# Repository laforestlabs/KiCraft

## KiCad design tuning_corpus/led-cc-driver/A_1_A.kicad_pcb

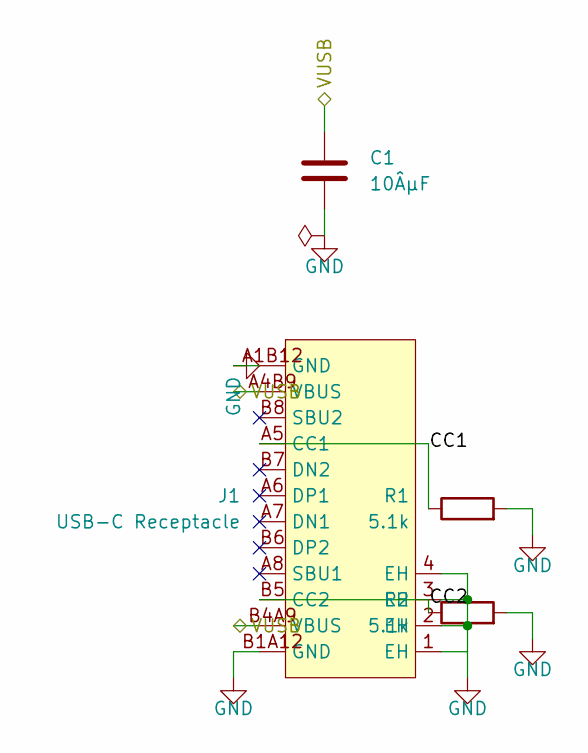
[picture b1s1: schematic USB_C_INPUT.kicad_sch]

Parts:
C1: 10ÂµF; C_0805_2012Metric
J1: USB-C Receptacle; USB-C_SMD-TYPE-C-31-M-12_1
R1, R2: 5.1k; R_0805_2012Metric

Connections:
CC1: J1.A5 (CC1), R1.1
CC2: J1.B5 (CC2), R2.1
GND: C1.2, J1.1 (EH), J1.2 (EH), J1.3 (EH), J1.4 (EH), J1.A1B12 (GND), J1.B1A12 (GND), R1.2, R2.2; also elsewhere on the board
VUSB: C1.1, J1.A4B9 (VBUS), J1.B4A9 (VBUS); also elsewhere on the board

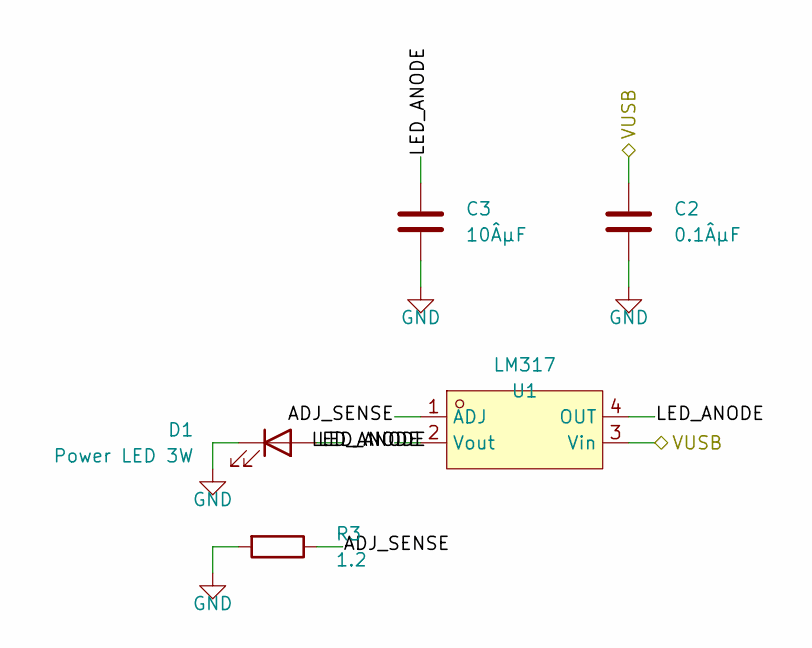
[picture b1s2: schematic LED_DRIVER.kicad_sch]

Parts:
C2: 0.1ÂµF; C_0805_2012Metric
C3: 10ÂµF; C_0805_2012Metric
D1: Power LED 3W; LED_Cree-PLCC4_5x5mm_CW
R3: 1.2; R_2512_6332Metric
U1: LM317; SOT-223-4_L6.5-W3.5-P2.30-LS7.0-BR

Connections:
ADJ_SENSE: R3.1, U1.1 (ADJ)
GND: C2.2, C3.2, D1.1 (K), R3.2; also elsewhere on the board
LED_ANODE: C3.1, D1.2 (A), U1.2 (Vout), U1.4 (OUT)
VUSB: C2.1, U1.3 (Vin); also elsewhere on the board

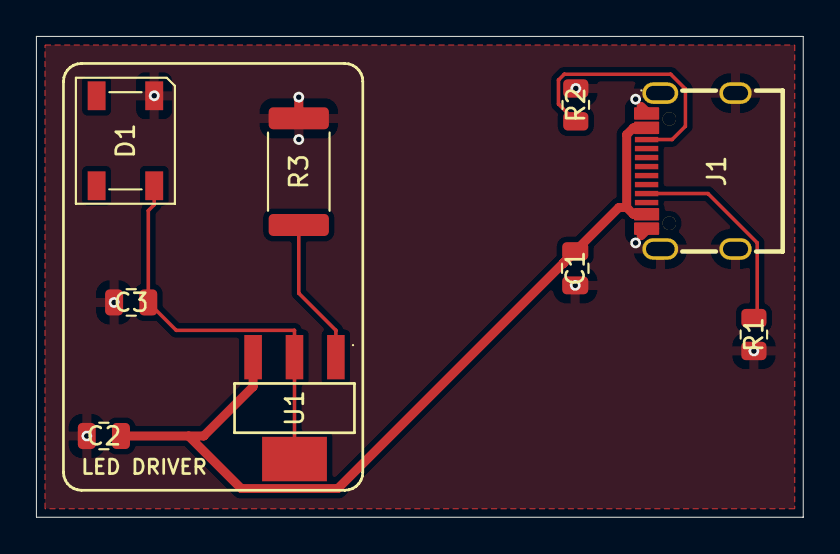
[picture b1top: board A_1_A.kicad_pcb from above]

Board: 2 copper layers, 42.6 x 26.7 mm, 9 parts (0 on the bottom side), 6 nets.

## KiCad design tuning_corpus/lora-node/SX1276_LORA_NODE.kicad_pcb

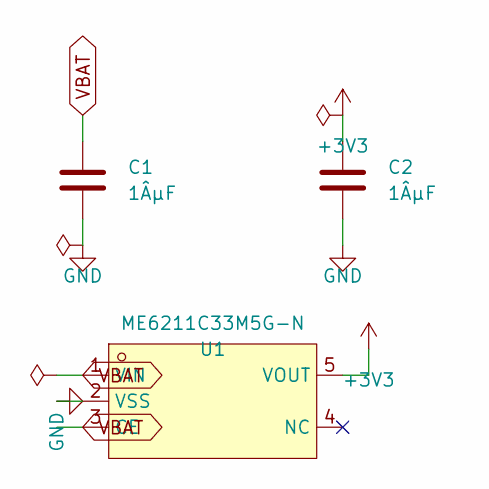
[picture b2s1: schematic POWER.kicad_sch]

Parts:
C1, C2: 1ÂµF; C_0805_2012Metric
U1: ME6211C33M5G-N; SOT-23-5_L3.0-W1.7-P0.95-LS2.8-BL

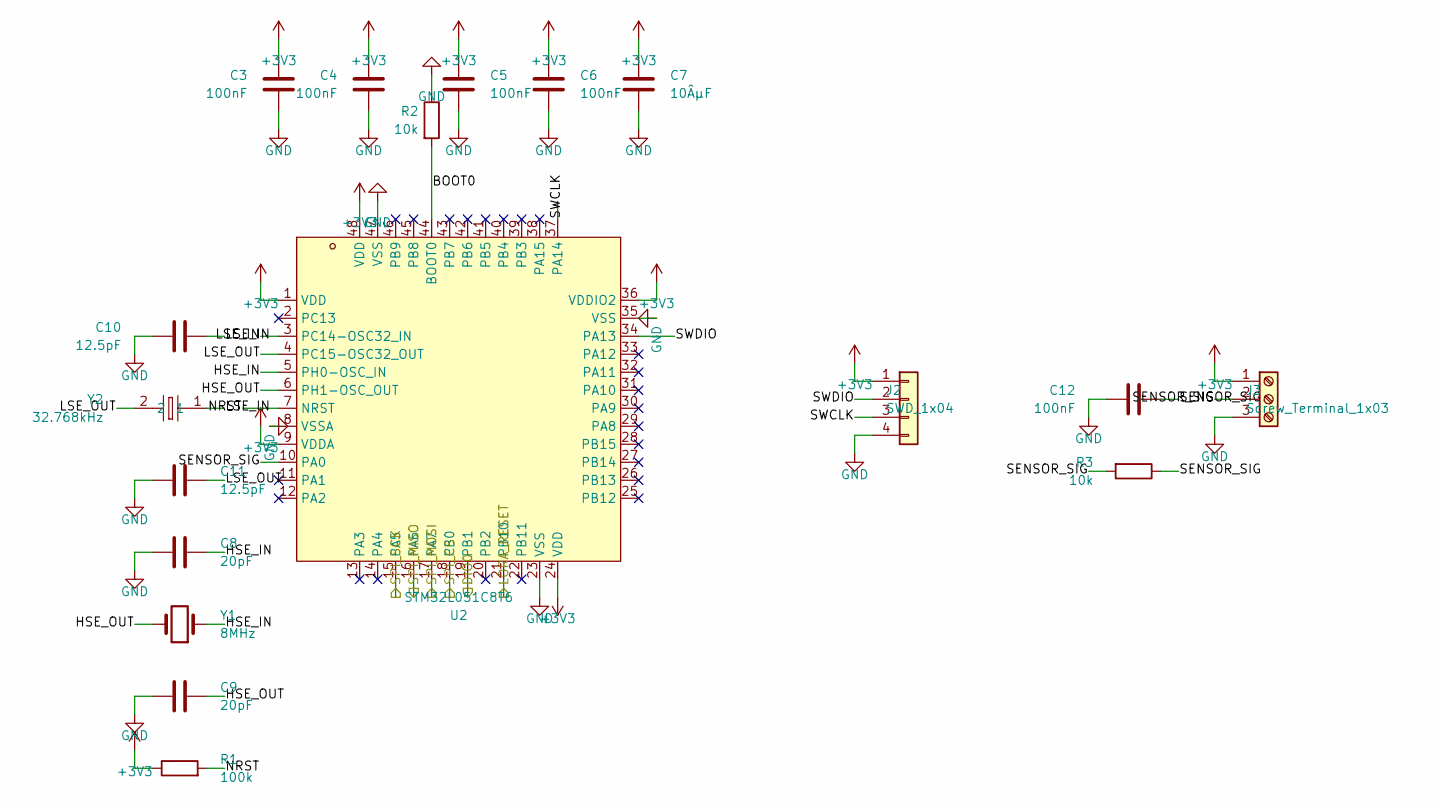
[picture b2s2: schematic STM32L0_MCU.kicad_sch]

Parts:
C3, C4, C5, C6, C12: 100nF; C_0805_2012Metric
C7: 10ÂµF; C_0805_2012Metric
C8, C9: 20pF; C_0805_2012Metric
C10, C11: 12.5pF; C_0805_2012Metric
J2: SWD_1x04; PinHeader_1x04_P2.54mm_Vertical
J3: Screw_Terminal_1x03; TerminalBlock_MaiXu_MX126-5.0-03P_1x03_P5.00mm
R1: 100k; R_0805_2012Metric
R2, R3: 10k; R_0805_2012Metric
U2: STM32L051C8T6; LQFP-48_L7.0-W7.0-P0.50-LS9.0-BL
Y1: 8MHz; Crystal_SMD_3225-4Pin_3.2x2.5mm
Y2: 32.768kHz; OSC-SMD_L3.2-W1.5

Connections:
BOOT0: R2.2, U2.44 (BOOT0)
DIO0: U2.19 (PB1); also elsewhere on the board
HSE_IN: C8.1, U2.5 (PH0-OSC_IN), Y1.1
HSE_OUT: C9.1, U2.6 (PH1-OSC_OUT), Y1.2
LORA_RESET: U2.21 (PB10); also elsewhere on the board
LSE_IN: C10.1, U2.3 (PC14-OSC32_IN), Y2.1
LSE_OUT: C11.1, U2.4 (PC15-OSC32_OUT), Y2.2
NRST: R1.2, U2.7 (NRST)
SENSOR_SIG: C12.1, J3.2, R3.1, R3.2, U2.10 (PA0)
SPI_CS: U2.18 (PB0); also elsewhere on the board
SPI_MISO: U2.16 (PA6); also elsewhere on the board
SPI_MOSI: U2.17 (PA7); also elsewhere on the board
SPI_SCK: U2.15 (PA5); also elsewhere on the board
SWCLK: J2.3, U2.37 (PA14)
SWDIO: J2.2, U2.34 (PA13)

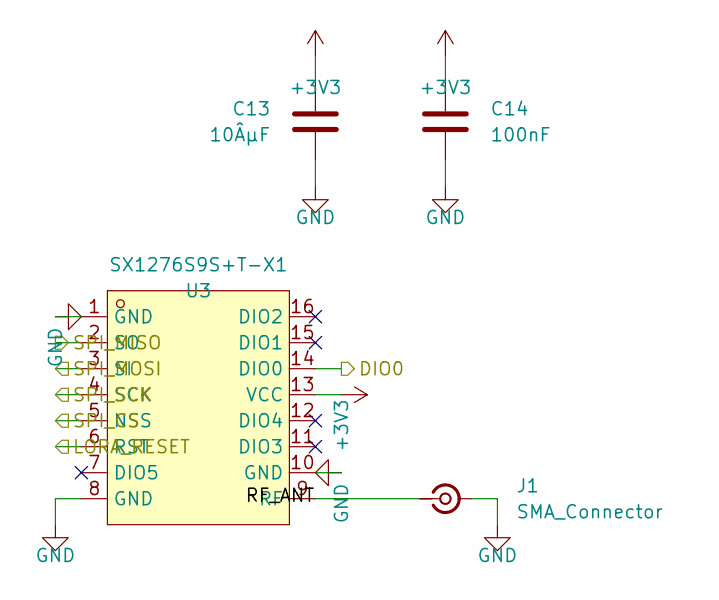
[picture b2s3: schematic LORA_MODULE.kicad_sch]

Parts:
C13: 10ÂµF; C_0805_2012Metric
C14: 100nF; C_0805_2012Metric
J1: SMA_Connector; SMA_Amphenol_132203-12_Horizontal
U3: SX1276S9S+T-X1; WIRELM-SMD_SX1278S165SY-T-X1

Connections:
DIO0: U3.14 (DIO0); also elsewhere on the board
LORA_RESET: U3.6 (RST); also elsewhere on the board
RF_ANT: J1.1 (In), U3.9 (RF)
SPI_CS: U3.5 (NSS); also elsewhere on the board
SPI_MISO: U3.2 (SO); also elsewhere on the board
SPI_MOSI: U3.3 (SI); also elsewhere on the board
SPI_SCK: U3.4 (SCK); also elsewhere on the board

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
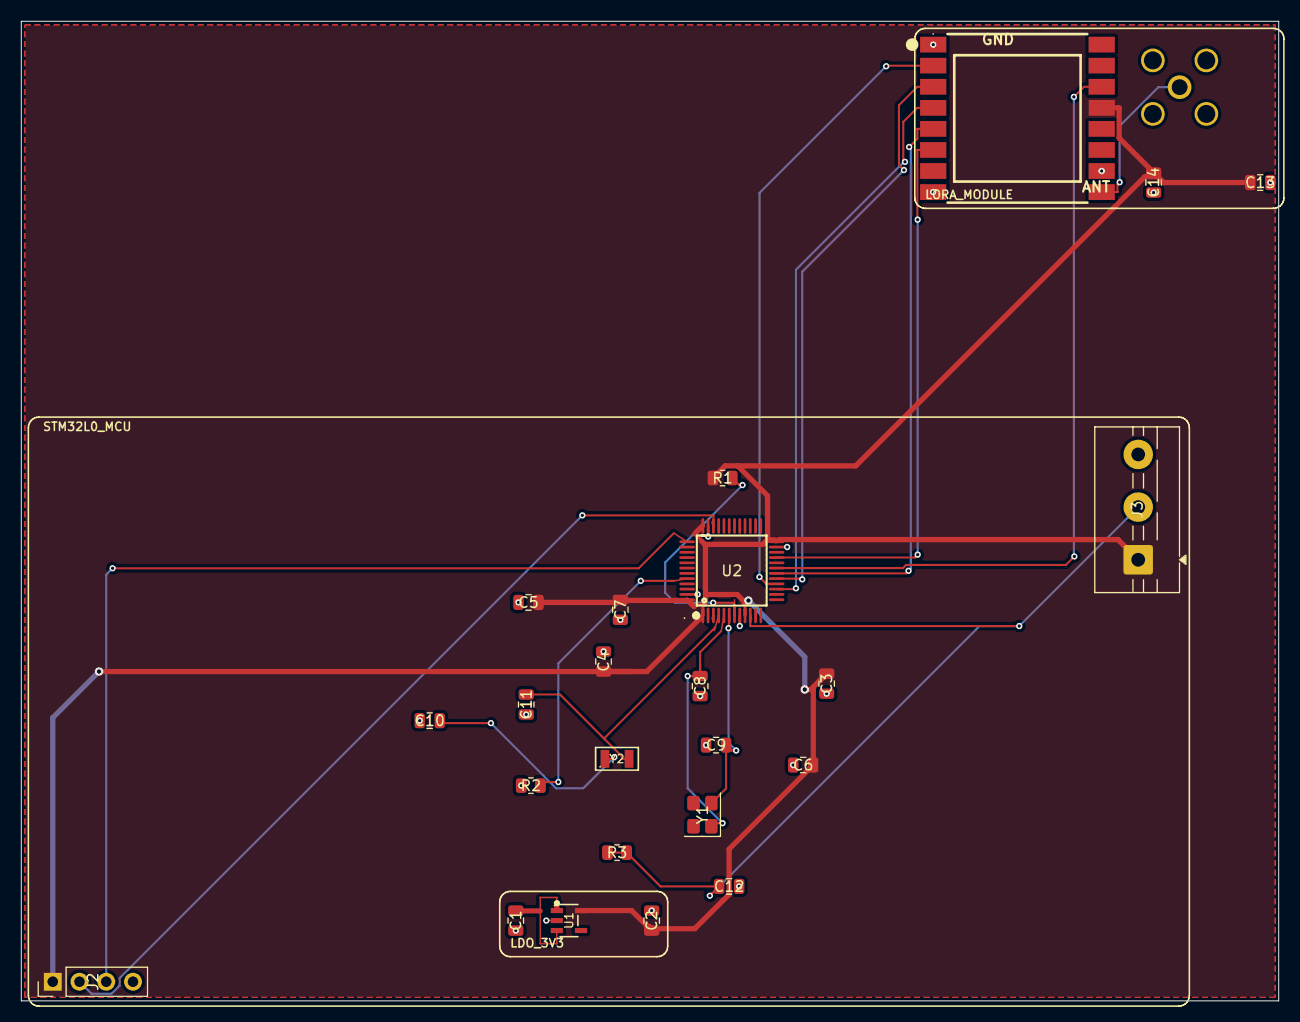
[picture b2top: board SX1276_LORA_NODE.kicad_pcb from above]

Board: 2 copper layers, 119.4 x 93.0 mm, 25 parts (1 on the bottom side), 19 nets.

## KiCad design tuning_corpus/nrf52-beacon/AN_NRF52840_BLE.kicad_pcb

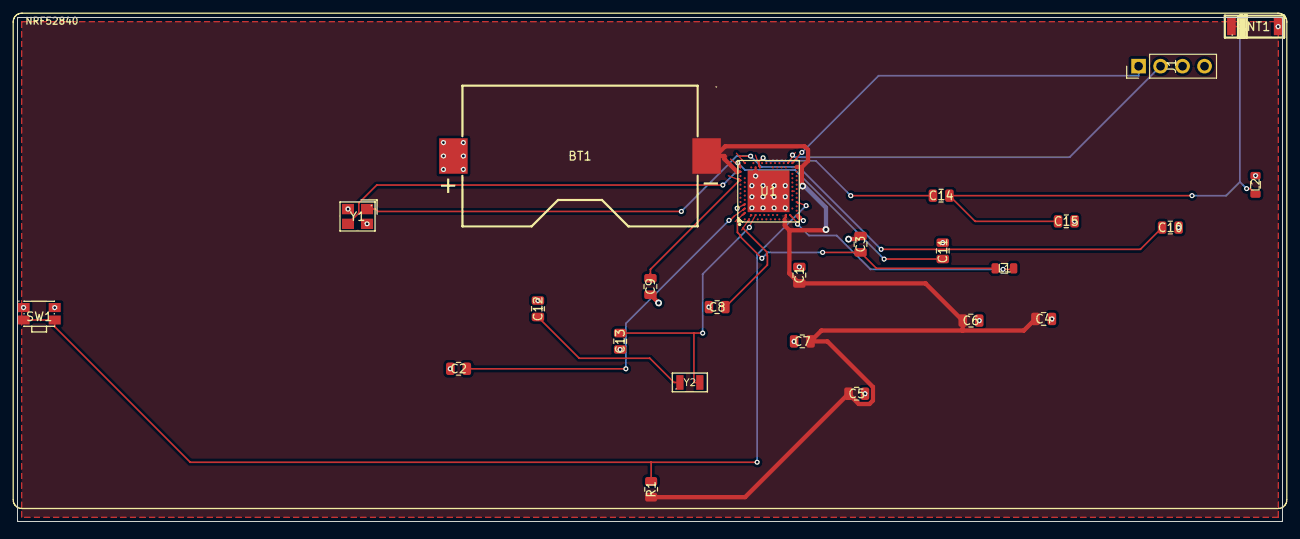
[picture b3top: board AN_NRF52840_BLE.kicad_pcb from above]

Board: 2 copper layers, 146.2 x 58.2 mm, 25 parts (0 on the bottom side), 17 nets.

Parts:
ANT1: RFANT5220110A0T; FILTER-SMD_L5.2-W2.0-L
BT1: CR2032; BAT-SMD_BS06A3B0A006
C1, C3: 10ÂµF; C_0805_2012Metric
C2: 4.7ÂµF; C_0805_2012Metric
C4, C5, C6, C7, C8, C9: 100nF; C_0805_2012Metric
C10, C11: 20pF; C_0805_2012Metric
C12, C13: 10pF; C_0805_2012Metric
C14, C15: 1.5pF; C_0805_2012Metric
J1: SWD 1x04; PinHeader_1x04_P2.54mm_Vertical
L1: 10ÂµH; L_0805_2012Metric
L2: 3.9nH; L_0805_2012Metric
R1: 10kÎ©; R_0805_2012Metric
SW1: EVQP7A01P; SW-SMD_EVQP7A01P
U1: nRF52840-QIAA-R; AQFN-73_L7.0-W7.0-P0.50-BL-EP4.8
Y1: 32MHz; CRYSTAL-SMD_4P-L3.2-W2.5-BL
Y2: 32.768kHz; OSC-SMD_L3.2-W1.5

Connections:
ANT: C14.1, U1.H23
ANT_OUT: ANT1.1, C14.2, C15.1, L2.1
BUTTON: R1.2, SW1.2, SW1.2', U1.AD8
DCC: C3.1, L1.1, U1.B3
DCCH: L1.2, U1.AB2
DEC1: C8.1, U1.C1
DEC2: C9.1, U1.A18
DEC4: C2.1, U1.B5
GND: ANT1.2, BT1.2, C1.2, C2.2, C3.2, C4.2, C5.2, C6.2, C7.2, C8.2, C9.2, C10.2, C11.2, C12.2, C13.2, C15.2, J1.4, L2.2, SW1.1, SW1.1', U1.0, U1.AD2, U1.B7, U1.F23, Y1.2, Y1.4
RESET: J1.3, U1.AC13
SWCLK: J1.2, U1.AA24
SWDIO: J1.1, U1.AC24
VDD: BT1.1, C1.1, C4.1, C5.1, C6.1, C7.1, R1.1, U1.A22, U1.AD14, U1.AD23, U1.B1, U1.W1, U1.Y2
XC1_32M: C10.1, U1.B24, Y1.1
XC2_32M: C11.1, U1.A23, Y1.3
XL1_32K: C12.1, U1.D2, Y2.1
XL2_32K: C13.1, U1.F2, Y2.2

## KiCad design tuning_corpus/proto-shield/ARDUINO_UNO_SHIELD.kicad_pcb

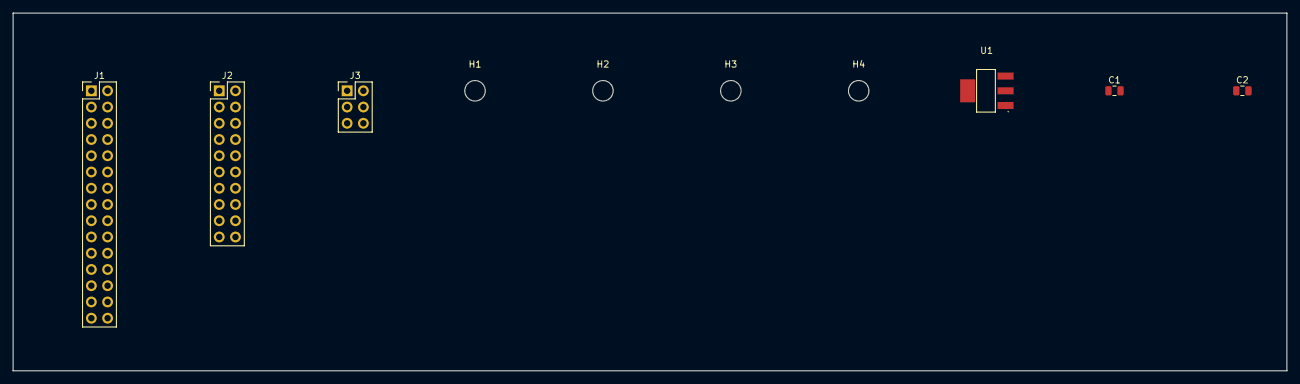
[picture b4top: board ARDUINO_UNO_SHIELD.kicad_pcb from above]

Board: 2 copper layers, 199.2 x 55.9 mm, 10 parts (0 on the bottom side), 17 nets, no tracks yet.

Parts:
C1, C2: 10uF; C_0805_2012Metric
H1, H2, H3, H4: Mounting Hole M3; MountingHole_3.2mm_M3
J1: Stacking Header 2x15; PinHeader_2x15_P2.54mm_Vertical
J2: Stacking Header 2x10; PinHeader_2x10_P2.54mm_Vertical
J3: ICSP Header 2x3; PinHeader_2x03_P2.54mm_Vertical
U1: AMS1117-3.3; SOT-223-3_L6.5-W3.4-P2.30-LS7.0-BR

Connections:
+3V3_ARDUINO: J1.9, J1.28, J2.9
+3V3_REG: C2.1, J2.11, U1.2, U1.4
+5V: C1.1, J1.1, J1.5, J2.1, J2.5, J3.2, U1.3
A0: J1.12, J2.12
A1: J1.14, J2.14
A2: J1.16, J2.16
A3: J1.18, J2.18
A4: J1.20, J2.20
AREF: J1.6, J2.6
D11: J1.23, J3.4
D12: J1.25, J3.1
D13: J1.27, J3.3
GND: C1.2, C2.2, J1.2, J1.7, J1.29, J1.30, J2.2, J2.7, J3.6, U1.1
RESET: J1.3, J2.3, J3.5
SCL: J1.10, J2.10
SDA: J1.8, J2.8
VIN: J1.4, J2.4

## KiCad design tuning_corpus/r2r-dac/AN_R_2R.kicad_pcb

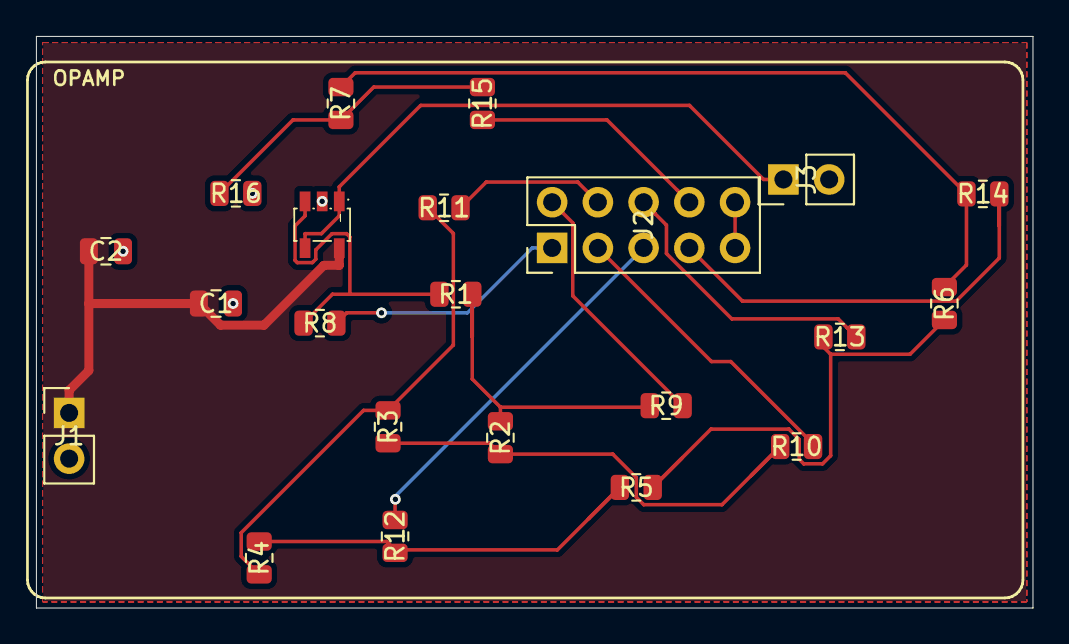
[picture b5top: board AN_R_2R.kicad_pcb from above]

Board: 2 copper layers, 55.4 x 31.8 mm, 22 parts (0 on the bottom side), 19 nets.

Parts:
C1: 0.1uF; C_0805_2012Metric
C2: 10uF; C_0805_2012Metric
J1: Power_2x1; PinHeader_1x02_P2.54mm_Vertical
J2: Input_2x05; PinHeader_2x05_P2.54mm_Vertical
J3: Output_2x1; PinHeader_1x02_P2.54mm_Vertical
R1, R2, R3, R4, R5, R6, R7: 10k; R_0805_2012Metric
R8, R9, R10, R11, R12, R13, R14, R15, R16: 20k; R_0805_2012Metric
U1: MCP6001T-I/OT; SOT-23-5_L3.0-W1.7-P0.95-LS2.8-BR

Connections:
+5V: C1.1, C2.1, J1.1, U1.5
ANA_OUT: J3.1, U1.1, U1.4
D0: J2.8, R15.2
D1: J2.7, R14.2
D2: J2.6, R13.2
D3: J2.5, R12.2
D4: J2.4, R11.2
D5: J2.3, R10.2
D6: J2.2, R9.2
D7: J2.1, R8.2
GND: C1.2, C2.2, J1.2, J2.9, J2.10, J3.2, R16.2, U1.2
N2: R1.2, R2.1, R9.1
N3: R2.2, R3.1, R10.1
N4: R3.2, R4.1, R11.1
N5: R4.2, R5.1, R12.1
N6: R5.2, R6.1, R13.1
N7: R6.2, R7.1, R14.1
N8: R7.2, R15.1, R16.1
VOUT: R1.1, R8.1, U1.3

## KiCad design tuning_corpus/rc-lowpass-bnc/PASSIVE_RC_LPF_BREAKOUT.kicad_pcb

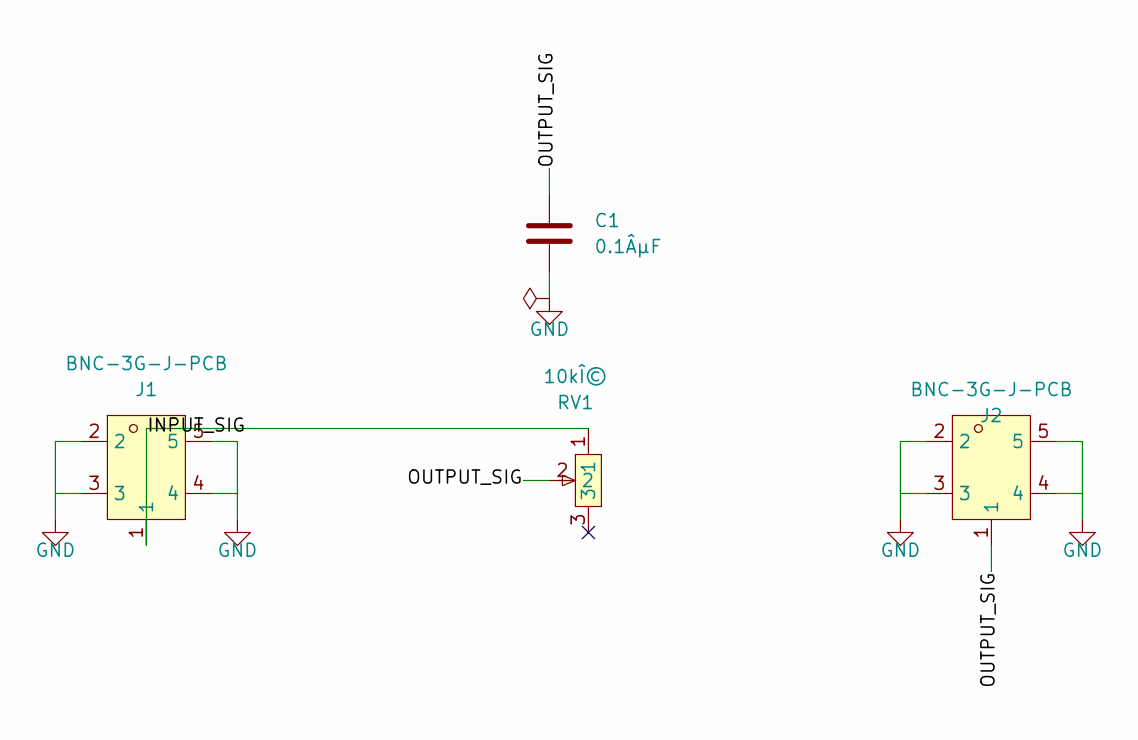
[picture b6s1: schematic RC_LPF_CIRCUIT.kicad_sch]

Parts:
C1: 0.1ÂµF; C_0805_2012Metric
J1, J2: BNC-3G-J-PCB; BNC-TH_BNC-3G-J-PCB
RV1: 10kÎ©; RES-ADJ-TH_3296W

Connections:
GND: C1.2, J1.2, J1.3, J1.4, J1.5, J2.2, J2.3, J2.4, J2.5
INPUT_SIG: J1.1, RV1.1
OUTPUT_SIG: C1.1, J2.1, RV1.2

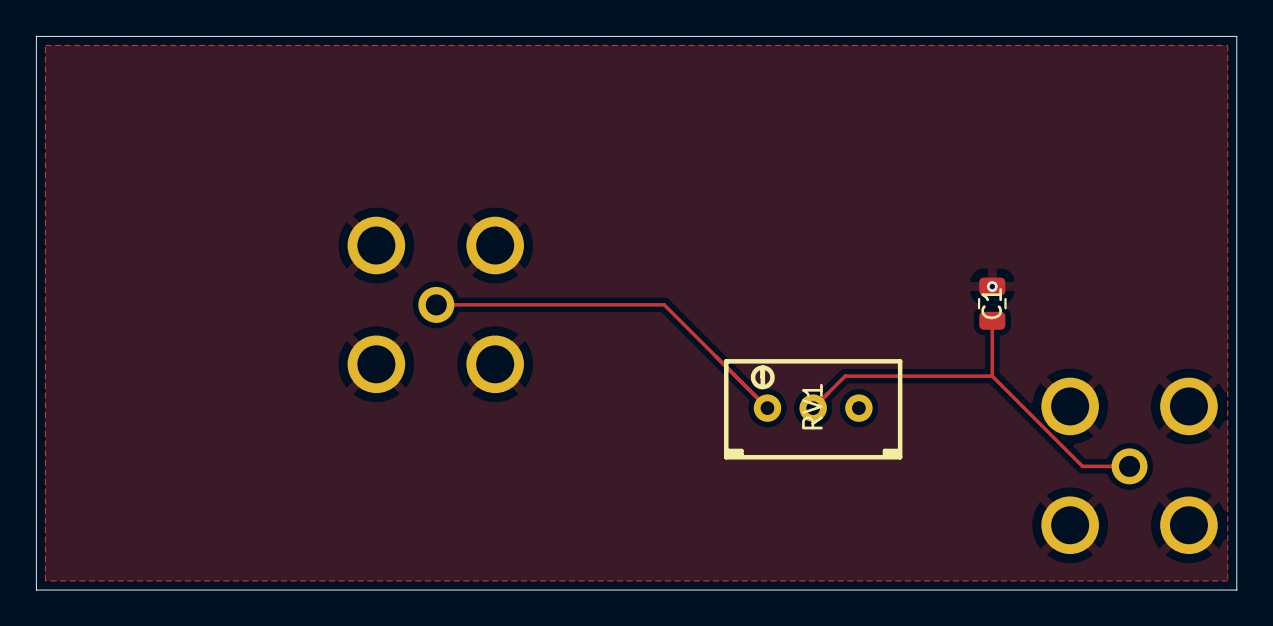
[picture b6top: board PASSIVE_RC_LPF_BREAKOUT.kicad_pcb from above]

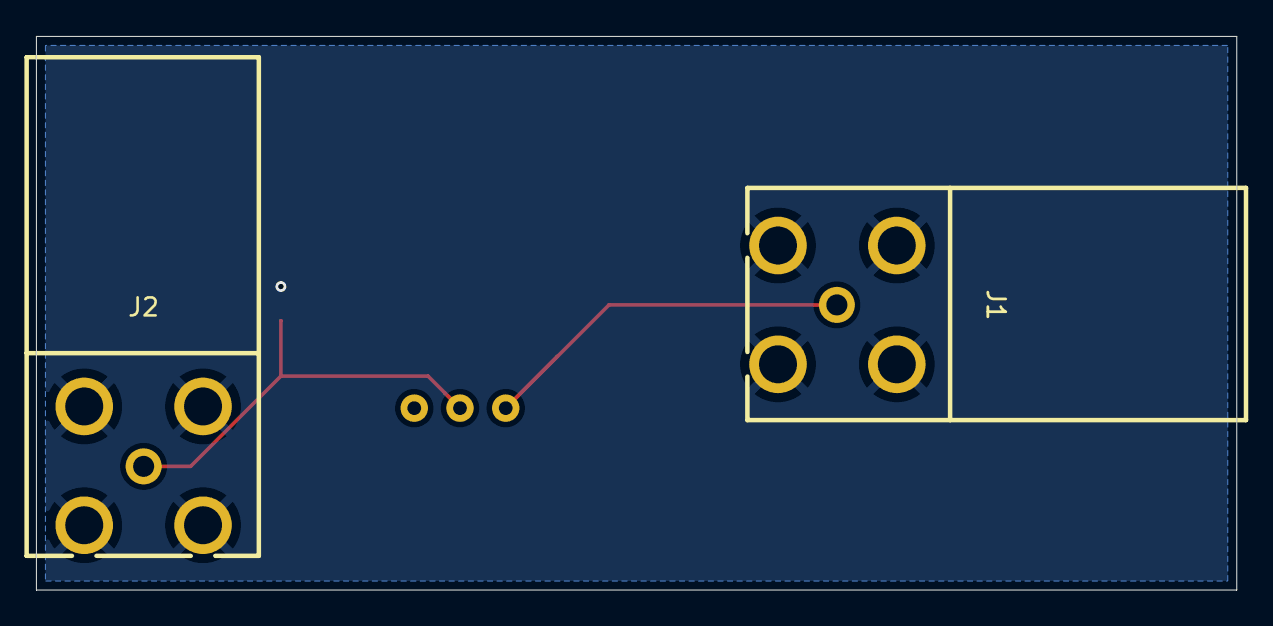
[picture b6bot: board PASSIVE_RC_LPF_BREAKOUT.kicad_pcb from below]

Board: 2 copper layers, 66.7 x 30.8 mm, 4 parts (2 on the bottom side), 3 nets.

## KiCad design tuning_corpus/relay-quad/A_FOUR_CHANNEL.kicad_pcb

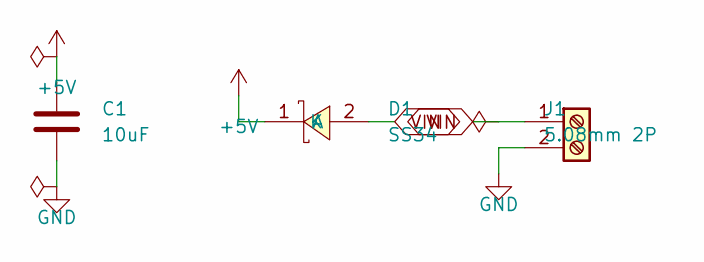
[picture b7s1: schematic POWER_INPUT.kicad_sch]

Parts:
C1: 10uF; C_0805_2012Metric
D1: SS34; SMA_L4.3-W2.6-LS5.2-RD
J1: 5.08mm 2P; TerminalBlock_CUI_TB007-508-02_1x02_P5.08mm_Horizontal

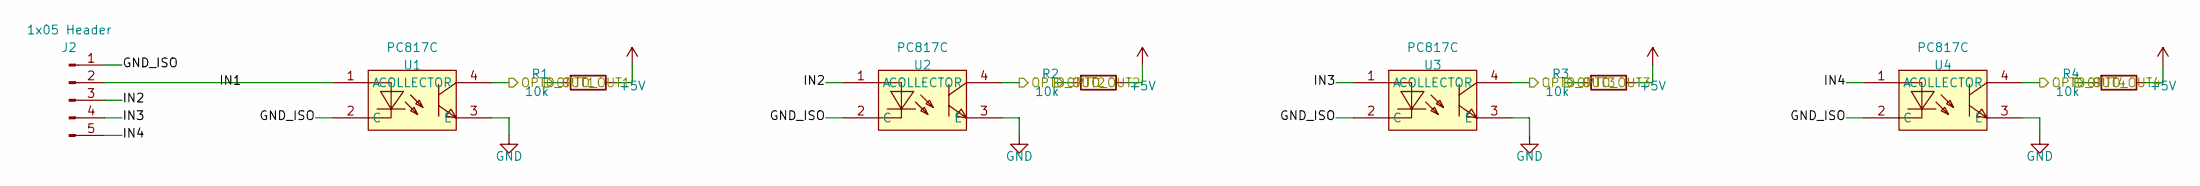
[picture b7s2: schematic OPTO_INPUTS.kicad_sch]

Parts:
J2: 1x05 Header; PinHeader_1x05_P2.54mm_Vertical
R1, R2, R3, R4: 10k; R_0805_2012Metric
U1, U2, U3, U4: PC817C; DIP-4_L6.5-W4.6-P2.54-LS7.6-BL

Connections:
GND_ISO: J2.1, U1.2 (C), U2.2 (C), U3.2 (C), U4.2 (C)
IN1: J2.2, U1.1 (A)
IN2: J2.3, U2.1 (A)
IN3: J2.4, U3.1 (A)
IN4: J2.5, U4.1 (A)
OPTO_OUT1: R1.2, U1.4 (COLLECTOR); also elsewhere on the board
OPTO_OUT2: R2.2, U2.4 (COLLECTOR); also elsewhere on the board
OPTO_OUT3: R3.2, U3.4 (COLLECTOR); also elsewhere on the board
OPTO_OUT4: R4.2, U4.4 (COLLECTOR); also elsewhere on the board

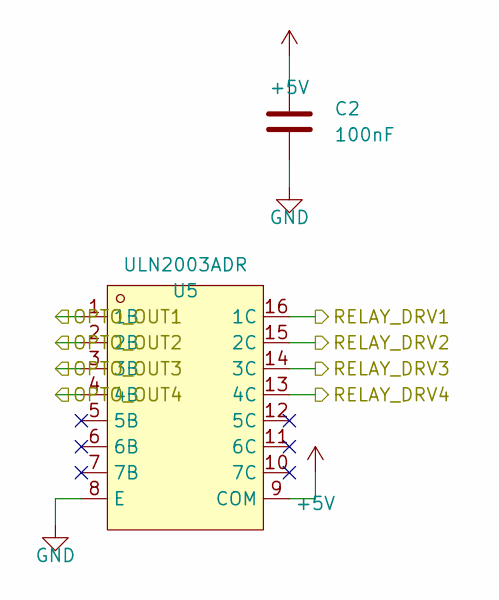
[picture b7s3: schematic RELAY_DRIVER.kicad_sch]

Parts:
C2: 100nF; C_0805_2012Metric
U5: ULN2003ADR; SOIC-16_L9.9-W3.9-P1.27-LS6.0-BL

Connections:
OPTO_OUT1: U5.1 (1B); also elsewhere on the board
OPTO_OUT2: U5.2 (2B); also elsewhere on the board
OPTO_OUT3: U5.3 (3B); also elsewhere on the board
OPTO_OUT4: U5.4 (4B); also elsewhere on the board
RELAY_DRV1: U5.16 (1C); also elsewhere on the board
RELAY_DRV2: U5.15 (2C); also elsewhere on the board
RELAY_DRV3: U5.14 (3C); also elsewhere on the board
RELAY_DRV4: U5.13 (4C); also elsewhere on the board

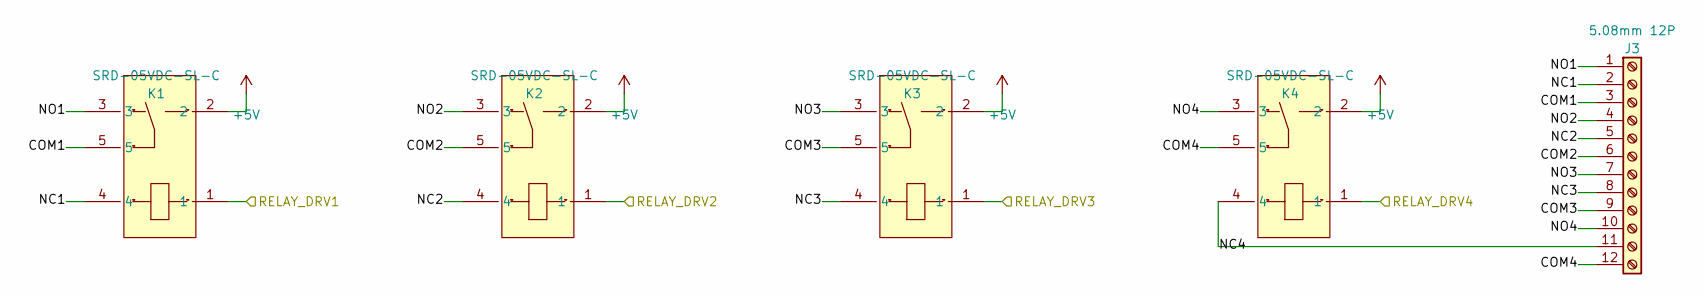
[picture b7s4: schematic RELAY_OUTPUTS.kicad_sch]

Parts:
J3: 5.08mm 12P; TerminalBlock_CUI_TB007-508-12_1x12_P5.08mm_Horizontal
K1, K2, K3, K4: SRD-05VDC-SL-C; RELAY-TH_SRD-XXVDC-XL-C

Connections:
COM1: J3.3, K1.5
COM2: J3.6, K2.5
COM3: J3.9, K3.5
COM4: J3.12, K4.5
NC1: J3.2, K1.4
NC2: J3.5, K2.4
NC3: J3.8, K3.4
NC4: J3.11, K4.4
NO1: J3.1, K1.3
NO2: J3.4, K2.3
NO3: J3.7, K3.3
NO4: J3.10, K4.3
RELAY_DRV1: K1.1; also elsewhere on the board
RELAY_DRV2: K2.1; also elsewhere on the board
RELAY_DRV3: K3.1; also elsewhere on the board
RELAY_DRV4: K4.1; also elsewhere on the board

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
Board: 2 copper layers, 19 parts (0 on the bottom side), 28 nets, no tracks yet.

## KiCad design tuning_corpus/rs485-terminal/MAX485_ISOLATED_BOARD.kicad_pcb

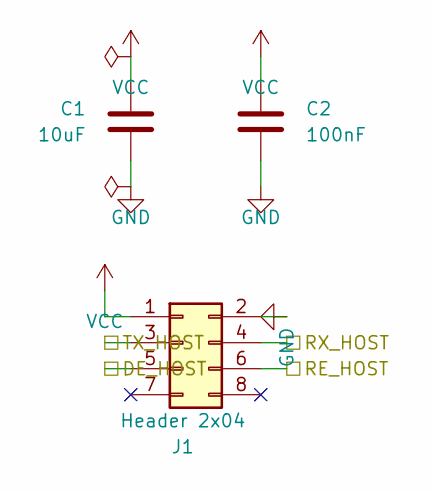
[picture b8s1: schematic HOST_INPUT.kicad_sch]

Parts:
C1: 10uF; C_0805_2012Metric
C2: 100nF; C_0805_2012Metric
J1: Header 2x04; PinHeader_2x04_P2.54mm_Vertical

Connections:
DE_HOST: J1.5; also elsewhere on the board
RE_HOST: J1.6; also elsewhere on the board
RX_HOST: J1.4; also elsewhere on the board
TX_HOST: J1.3; also elsewhere on the board

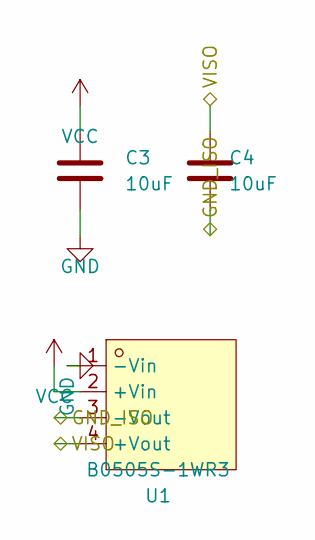
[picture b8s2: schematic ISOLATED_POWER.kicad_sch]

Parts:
C3, C4: 10uF; C_0805_2012Metric
U1: B0505S-1WR3; PWRM-TH_B0505S-1WR3

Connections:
GND_ISO: C4.2, U1.3 (-Vout); also elsewhere on the board
VISO: C4.1, U1.4 (+Vout); also elsewhere on the board

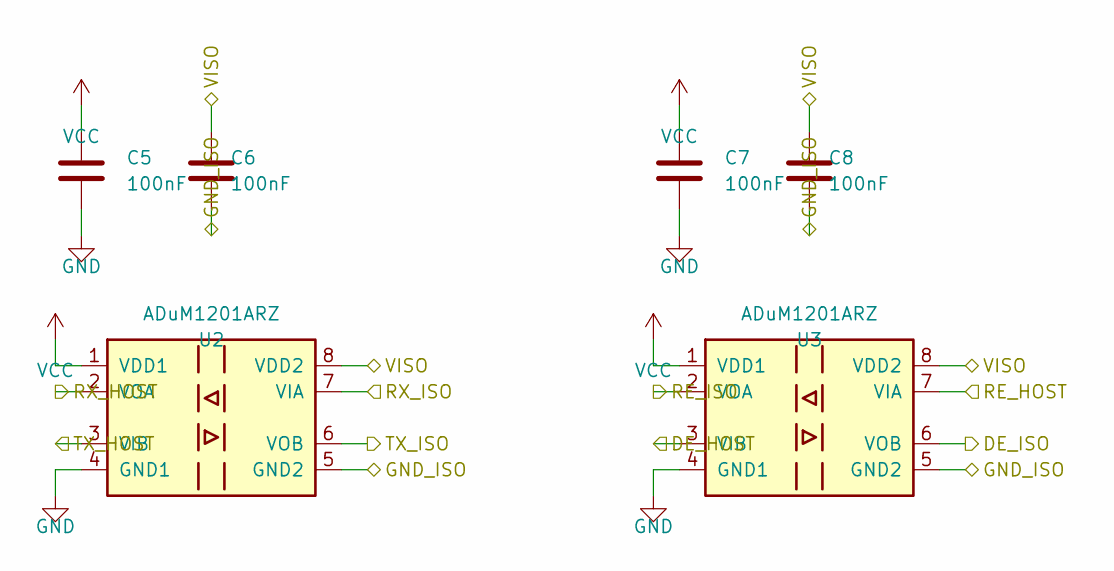
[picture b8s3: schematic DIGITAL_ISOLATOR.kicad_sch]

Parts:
C5, C6, C7, C8: 100nF; C_0805_2012Metric
U2, U3: ADuM1201ARZ; SOIC-8_3.9x4.9mm_P1.27mm

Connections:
DE_HOST: U3.3 (VIB); also elsewhere on the board
DE_ISO: U3.6 (VOB); also elsewhere on the board
GND_ISO: C6.2, C8.2, U2.5 (GND2), U3.5 (GND2); also elsewhere on the board
RE_HOST: U3.7 (VIA); also elsewhere on the board
RE_ISO: U3.2 (VOA); also elsewhere on the board
RX_HOST: U2.2 (VOA); also elsewhere on the board
RX_ISO: U2.7 (VIA); also elsewhere on the board
TX_HOST: U2.3 (VIB); also elsewhere on the board
TX_ISO: U2.6 (VOB); also elsewhere on the board
VISO: C6.1, C8.1, U2.8 (VDD2), U3.8 (VDD2); also elsewhere on the board
